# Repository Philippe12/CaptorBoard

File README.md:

# CaptorBoard
## Decription
Lite automated board with tow relai, one one wire for DHT11, one i2c busse, gpio and UART.
This board is build around a esp32 and designed for Esphome OS.

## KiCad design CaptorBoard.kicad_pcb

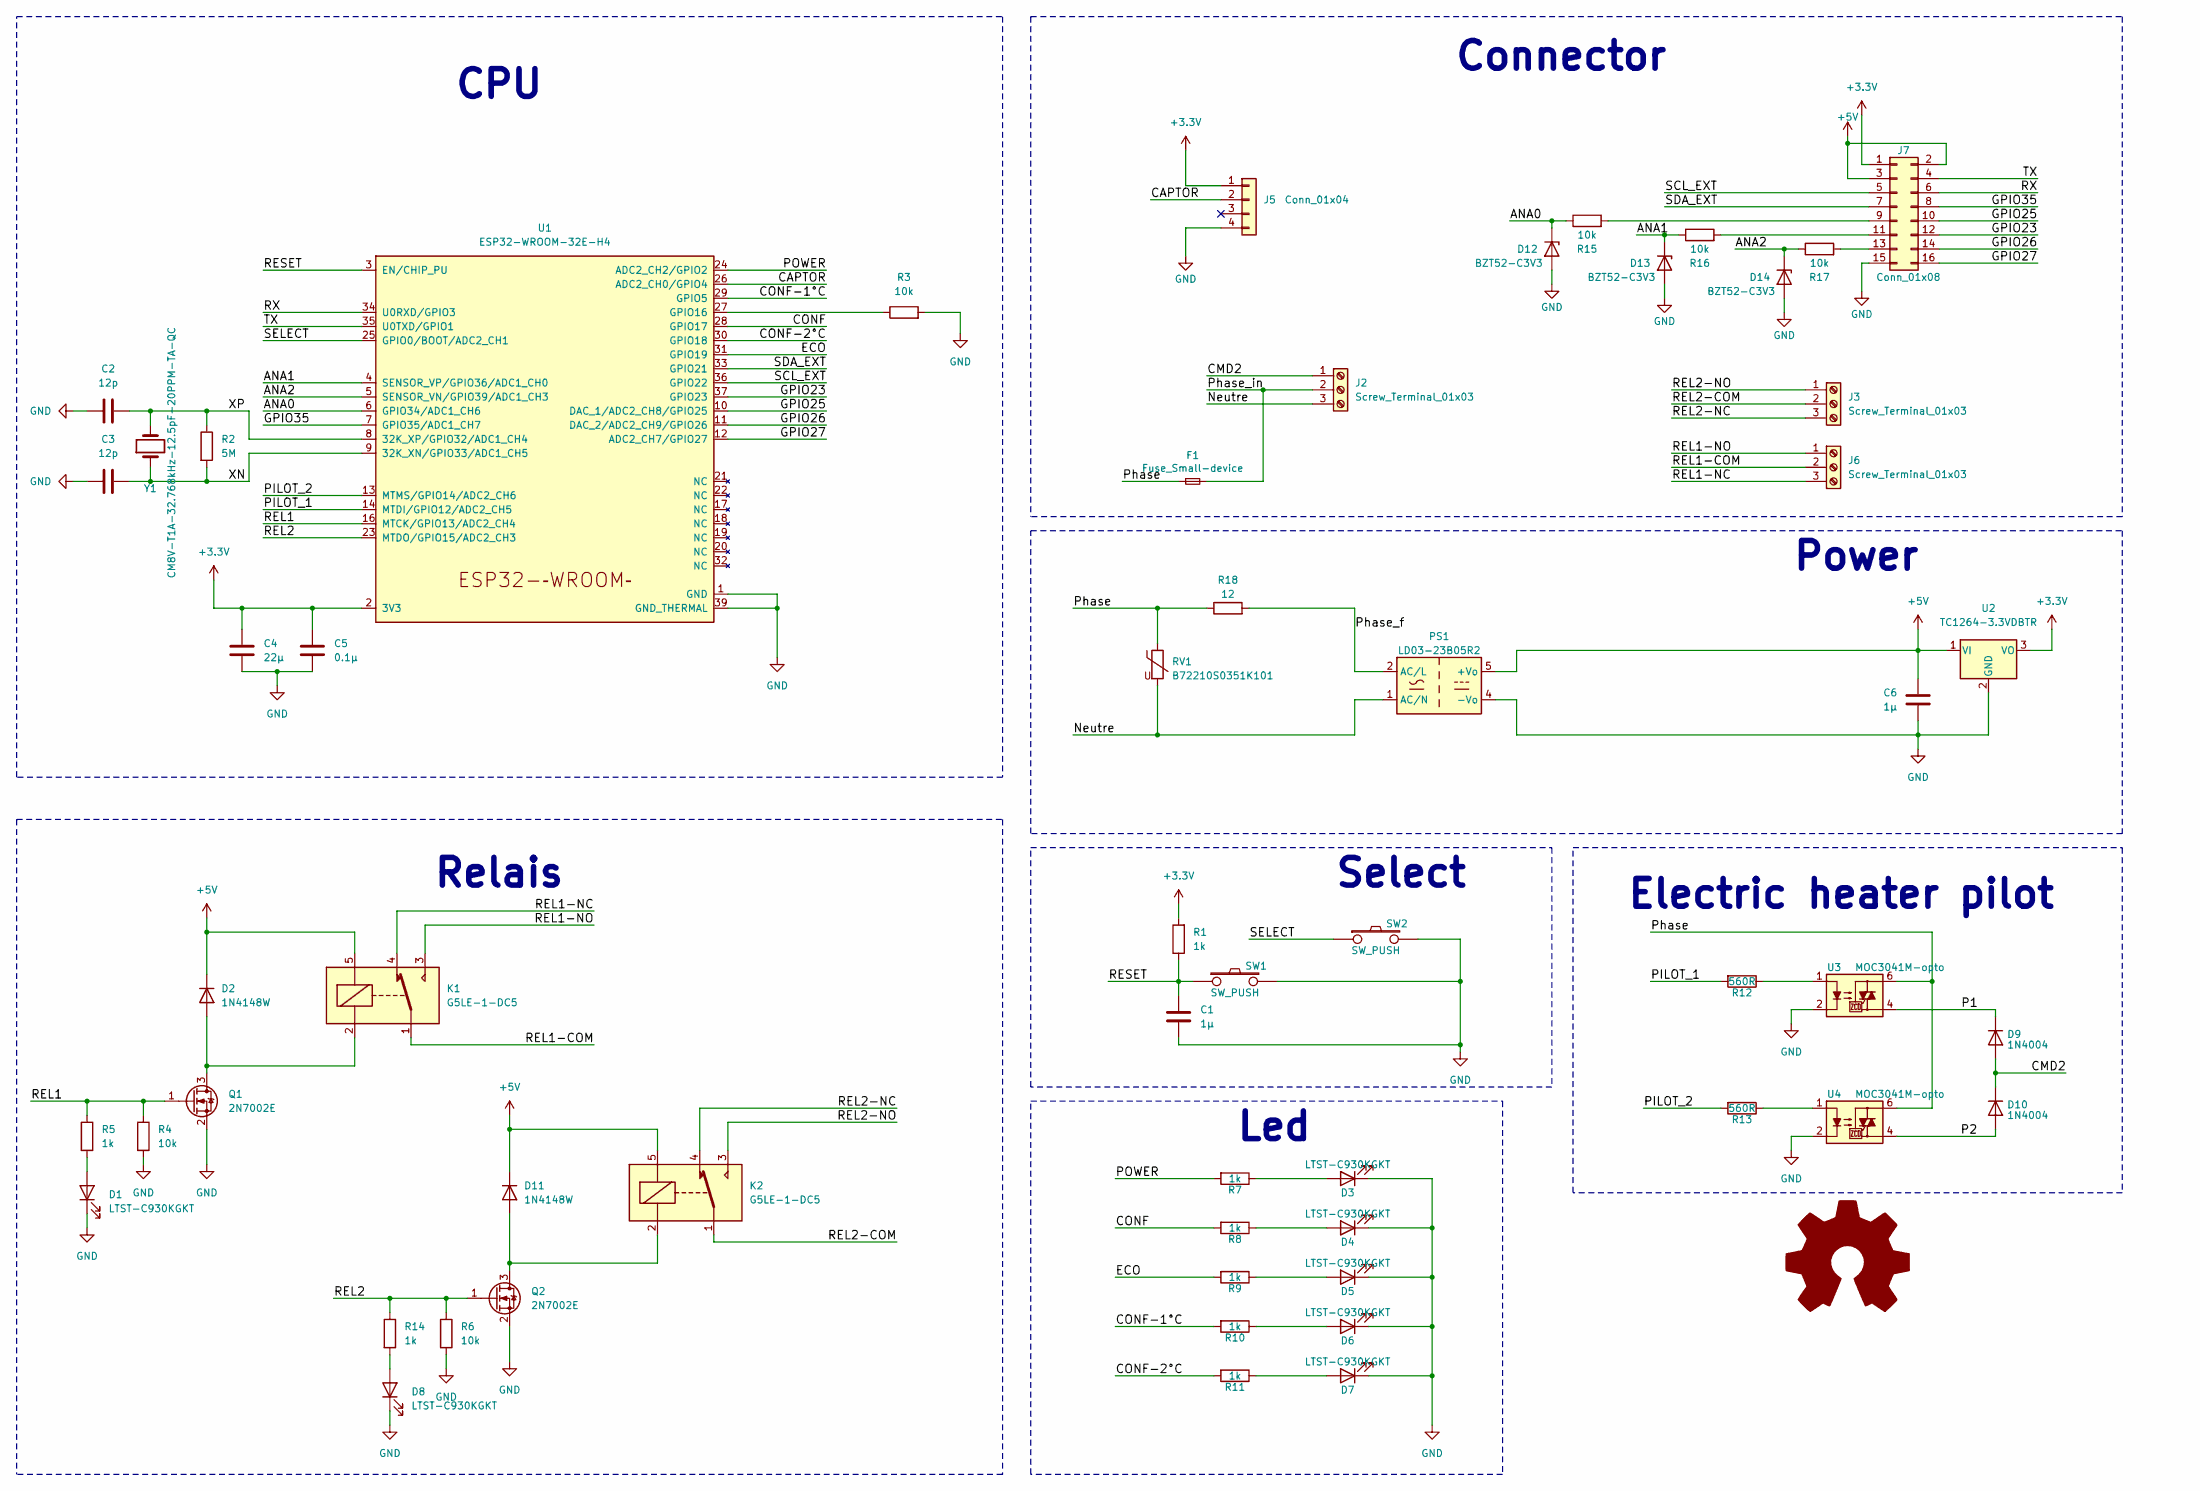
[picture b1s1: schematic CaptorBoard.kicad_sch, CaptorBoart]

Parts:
C1, C6: 1µ; C_1210_3225Metric_Pad1.33x2.70mm_HandSolder
C2, C3: 12p; C_1206_3216Metric_Pad1.33x1.80mm_HandSolder
C4: 22µ; C_1210_3225Metric_Pad1.33x2.70mm_HandSolder
C5: 0.1µ; C_1210_3225Metric_Pad1.33x2.70mm_HandSolder
D1, D3, D4, D5, D6, D7, D8: LTST-C930KGKT; LED_1210_3225Metric_Pad1.42x2.65mm_HandSolder
D2, D11: 1N4148W; D_SOD-123
D9, D10: 1N4004; D_DO-41_SOD81_P7.62mm_Horizontal
D12, D13, D14: BZT52-C3V3; D_SOD-123F
F1: Fuse_Small-device; Fuse_Schurter_UMT250
J2, J3, J6: Screw_Terminal_01x03; TerminalBlock_Phoenix_MKDS-1,5-3-5.08_1x03_P5.08mm_Horizont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
J5: Conn_01x04; PinHeader_1x04_P2.54mm_Vertical
J7: Conn_01x08; PinHeader_2x08_P2.54mm_Vertical
K1, K2: G5LE-1-DC5; Relay_SPDT_Omron-G5LE-1
PS1: LD03-23B05R2; PSK5D5
Q1, Q2: 2N7002E; SOT-23
R1, R5, R7, R8, R9, R10, R11, R14: 1k; R_1210_3225Metric_Pad1.30x2.65mm_HandSolder
R2: 5M; R_1210_3225Metric_Pad1.30x2.65mm_HandSolder
R3, R4, R6, R15, R16, R17: 10k; R_1210_3225Metric_Pad1.30x2.65mm_HandSolder
R12, R13: 560R; R_1210_3225Metric_Pad1.30x2.65mm_HandSolder
R18: 12; R_2512_6332Metric_Pad1.40x3.35mm_HandSolder
RV1: B72210S0351K101; RV_Disc_D12mm_W5.1mm_P7.5mm
SW1, SW2: SW_PUSH; SW_Tactile_SKHH_Angled
SYM1: Logo_Open_Hardware_Large; OSHW-Logo2_14.6x12mm_SilkScreen
U1: ESP32-WROOM-32E-H4; ESP32-WROOM-32E
U2: TC1264-3.3VDBTR; SOT-223-3_TabPin2
U3, U4: MOC3041M-opto; DIP-6_W7.62mm
Y1: CM8V-T1A-32.768kHz-12.5pF-20PPM-TA-QC; Crystal_SMD_MicroCrystal_CC8V-T1A-2Pin_2.0x1.2mm_HandSolder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

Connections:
+3.3V: C4.1, C5.1, J5.1, J7.1, R1.2, U1.2 (3V3), U2.3 (VO)
+5V: C6.1, D2.1 (K), D11.1 (K), J7.2, J7.3, K1.5, K2.5, PS1.5 (+Vo), U2.1 (VI)
/ANA0: D12.1 (K), R15.1, U1.6 (GPIO34/ADC1_CH6)
/ANA1: D13.1 (K), R16.1, U1.4 (SENSOR_VP/GPIO36/ADC1_CH0)
/ANA2: D14.1 (K), R17.1, U1.5 (SENSOR_VN/GPIO39/ADC1_CH3)
/CAPTOR: J5.2, U1.26 (ADC2_CH0/GPIO4)
/CMD2: D9.2 (A), D10.1 (K), J2.1
/CONF: R8.2, U1.28 (GPIO17)
/CONF-1°C: R10.2, U1.29 (GPIO5)
/CONF-2°C: R11.2, U1.30 (GPIO18)
/ECO: R9.2, U1.31 (GPIO19)
/GPIO23: J7.12, U1.37 (GPIO23)
/GPIO25: J7.10, U1.10 (DAC_1/ADC2_CH8/GPIO25)
/GPIO26: J7.14, U1.11 (DAC_2/ADC2_CH9/GPIO26)
/GPIO27: J7.16, U1.12 (ADC2_CH7/GPIO27)
/GPIO35: J7.8, U1.7 (GPIO35/ADC1_CH7)
/Neutre: J2.3, PS1.1 (AC/N), RV1.2
/P1: D9.1 (K), U3.4
/P2: D10.2 (A), U4.4
/PILOT_1: R12.2, U1.14 (MTDI/GPIO12/ADC2_CH5)
/PILOT_2: R13.2, U1.13 (MTMS/GPIO14/ADC2_CH6)
/POWER: R7.2, U1.24 (ADC2_CH2/GPIO2)
/Phase: F1.1, R18.1, RV1.1, U3.6, U4.6
/Phase_f: PS1.2 (AC/L), R18.2
/Phase_in: F1.2, J2.2
/REL1: Q1.1 (G), R4.1, R5.1, U1.16 (MTCK/GPIO13/ADC2_CH4)
/REL1-COM: J6.2, K1.1
/REL1-NC: J6.3, K1.4
/REL1-NO: J6.1, K1.3
/REL2: Q2.1 (G), R6.1, R14.1, U1.23 (MTDO/GPIO15/ADC2_CH3)
/REL2-COM: J3.2, K2.1
/REL2-NC: J3.3, K2.4
/REL2-NO: J3.1, K2.3
/RESET: C1.1, R1.1, SW1.1, U1.3 (EN/CHIP_PU)
/RX: J7.6, U1.34 (U0RXD/GPIO3)
/SCL_EXT: J7.5, U1.36 (GPIO22)
/SDA_EXT: J7.7, U1.33 (GPIO21)
/SELECT: SW2.1, U1.25 (GPIO0/BOOT/ADC2_CH1)
/TX: J7.4, U1.35 (U0TXD/GPIO1)
/XN: C3.2, R2.2, U1.9 (32K_XN/GPIO33/ADC1_CH5), Y1.1
/XP: C2.2, R2.1, U1.8 (32K_XP/GPIO32/ADC1_CH4), Y1.2
GND: C1.2, C2.1, C3.1, C4.2, C5.2, C6.2, D1.1 (K), D3.1 (K), D4.1 (K), D5.1 (K), D6.1 (K), D7.1 (K), D8.1 (K), D12.2 (A), D13.2 (A), D14.2 (A), J5.4, J7.15, PS1.4 (-Vo), Q1.2 (S), Q2.2 (S), R3.2, R4.2, R6.2, SW1.2, SW2.2, U1.1 (GND), U1.15 (GND), U1.38 (GND), U1.39 (GND_THERMAL), U2.2 (GND), U3.2, U4.2
unnamed: D1.2 (A), R5.2
unnamed: D2.2 (A), K1.2, Q1.3 (D)
unnamed: D3.2 (A), R7.1
unnamed: D4.2 (A), R8.1
unnamed: D5.2 (A), R9.1
unnamed: D6.2 (A), R10.1
unnamed: D7.2 (A), R11.1
unnamed: D8.2 (A), R14.2
unnamed: D11.2 (A), K2.2, Q2.3 (D)
unnamed: J7.9, R15.2
unnamed: J7.11, R16.2
unnamed: J7.13, R17.2
unnamed: R12.1, U3.1
unnamed: R13.1, U4.1
unnamed: R3.1, U1.27 (GPIO16)

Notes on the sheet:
Power
Led
CPU
Select
Electric heater pilot
Connector
Relais

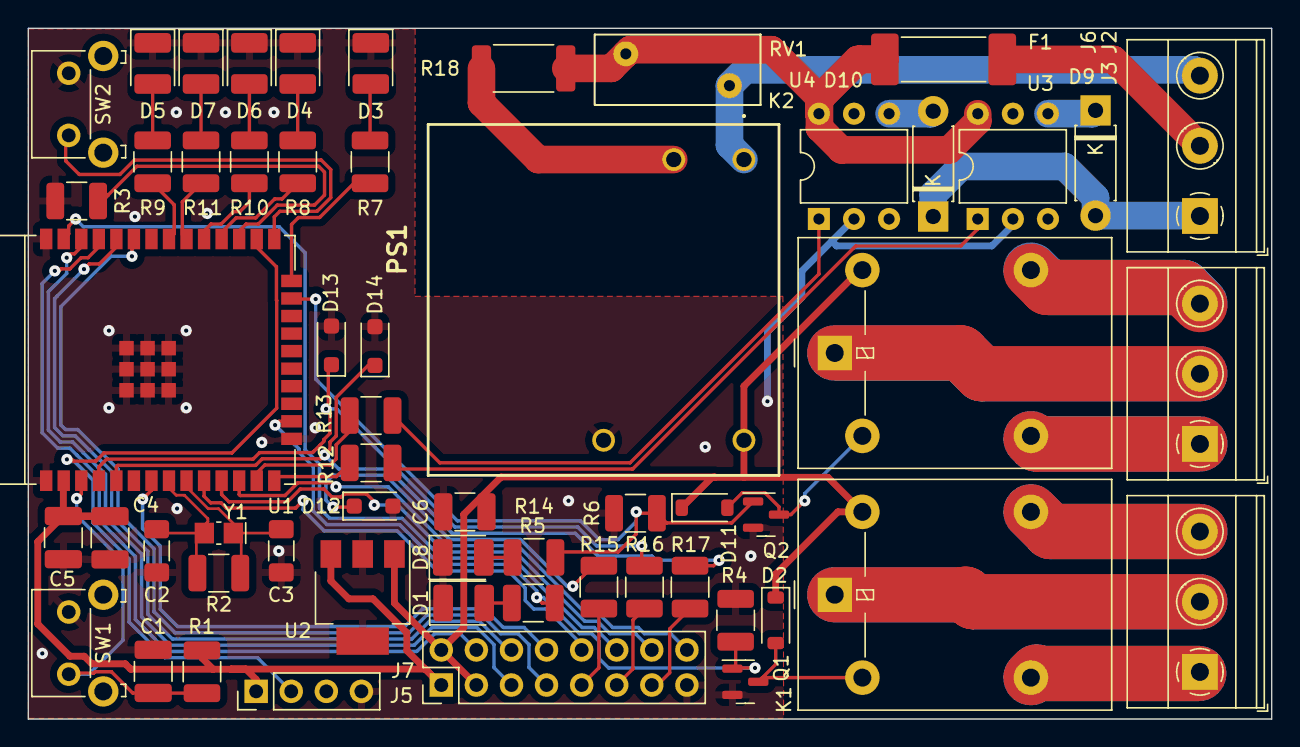
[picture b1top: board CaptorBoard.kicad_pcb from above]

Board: 2 copper layers, 90.0 x 50.0 mm, 58 parts (1 on the bottom side), 57 nets.

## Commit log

2015-02-15 Add eagle project
2015-02-15 Add SHT25 package
2015-02-15 Add .gitignore
2015-02-15 Add SHT25 to shema
2015-02-18 Update ignore
2015-02-18 Add net USBID
2015-02-18 Add project
2015-02-19 Add I2C bus for SHT25
2015-02-19 Add MPL115A2 in lib
2015-02-19 Add MRF24J40MA in lib
2015-02-21 Add MPL115A2 to schematic
2015-02-21 Update MPL115A2
2015-02-21 Change placement
2015-02-21 Add MRF24J40MA to schematic
2015-03-21 Add electric radiator pilot function
2015-03-22 Change all presentation an add a frame
2015-03-22 Add ZSR330GTA chip
2015-03-22 Revert "Add ZSR330GTA chip"
    This reverts commit 198221634bf1fdf5ee97219015ade1a2120c0af6.
2015-03-22 Add TC1262-3.3VDB chip to lib
2015-03-22 Add 3,3V decoupling capacitor
2015-03-29 Add VTX-214-003-105 power AD/DC converter
2015-03-29 Update VTX-214-003-105 and SHT25 for displaying just the pin name
2015-03-29 Insert Power convertor
2015-03-30 insert led
2015-03-30 Change command PILOT_x from std output to PWM output
2015-03-30 Move button to int input
2015-03-30 Change PHOENIX connector type
2015-03-31 Small change for better display
2015-04-04 Some correction
2015-04-06 Correct the PIC32MX bin asignement
2015-04-09 Large change convert project to Kickad It is better to use a open sources project
2015-04-09 Set all foot print
2015-04-19 Change LED foot print Add extension conector
2015-04-19 Add data sheet
2015-04-19 Some foot print
2015-04-19 remove autosave file
2015-04-19 Ignore some file
2015-04-19 Some ERC correction
2015-04-19 Change led pin order for routing facility
2015-04-21 Place Fuse before all
2015-04-21 Change converter AC/DC The old one to height for the case
2015-04-21 Led guide line
2015-04-21 Ignore
2015-04-21 Forgot foot print
2015-04-21 Add marker for 5V
2015-04-23 Change HST21
2015-04-23 First PCB
2015-04-24 Change data sheet
2015-04-25 3D form
2015-04-25 Change mark position
2015-04-26 Replace Value 550 ohm to 560ohm (mormailsition)
2015-04-26 Error of ref
2015-04-26 New bom
2015-05-04 Change led package to 3mm
2015-05-04 Change RH/temp sensor to STH21
2015-05-04 Change Button ref
2017-12-18 last version
2018-07-26 finally use WeMos Mini
2020-06-21 Board final
2020-11-19 ignore backup
2020-11-19 new kicad version
2020-11-19 production files
2020-12-10 add pull up for booting conditions
2021-04-21 with new kicad version
2021-12-02 new kicad
2022-11-18 Add new datasheet
2022-11-18 Add new 3D
2022-11-18 Add new lib
2022-11-18 Add new footprint
2022-11-18 Remove wemos D1 for ESP32-WROOM-32
2022-11-18 New routing
2022-11-18 remove unuse file
2022-11-21 move sector track for more isolating
2022-11-21 Change routing and add logo
2022-11-25 update ref
2022-11-28 add serigraphie
2022-11-28 remove bad net
2022-12-01 New desing
2022-12-01 Add doc
2022-12-01 update bon and cost
2022-12-08 Optimize routing
2022-12-08 Add open source hardware logo
2022-12-23 use only step file for 3D render
2022-12-23 Add 3D export
2023-01-06 Adjust some routing
2023-01-19 change litbite routing
2023-01-19 Add picture to documentation
2023-01-19 Add production file
2023-01-20 Change relait and LED schematic
2023-01-20 new production files export
2023-01-20 update image for read me
2023-01-26 Add top and bottom track for relais output
2023-01-30 review routing
2023-01-30 Export/Update 3D images for documentation
2023-01-30 Update production files
2023-03-17 To kicad 7
2023-04-02 Add new component into lib
2023-04-02 Change AC/DC converter for one smaller and chiper
2023-04-02 route new converter
2023-04-02 update bom
2023-04-02 udate 3D render
2023-04-02 update production file
2023-04-13 Add split for isolation on relais contact side
2023-04-13 Update picture
2023-05-01 Change somme manufacturer referance
2023-05-01 remove some via
2023-05-01 change power label name because their are not the same
2023-05-01 update manufacturer reference into pcb
2023-06-07 Add two more anlog input and protect it
2023-06-07 route the new analog input and protections
2023-06-07 new image for documentation
2023-06-07 new production files
2023-06-22 Change connecteur and pin for a better routing
2023-06-22 optimize route
2023-06-22 update images
2023-06-22 generate procution file
2023-06-24 change route
2023-06-24 add digikey cote
2023-06-28 add CEM protection, and change reférance for Digikey distributor
2023-07-10 change a bad foot print for fuse
2023-07-10 new prod file
2023-07-23 LED it inversed
2023-08-26 Change ANA0 ESP32 input the ADC2 is not use-able if the WIFI is active
2023-08-26 route AN0 channel
2024-05-08 Migrate to Kicad 8.0
